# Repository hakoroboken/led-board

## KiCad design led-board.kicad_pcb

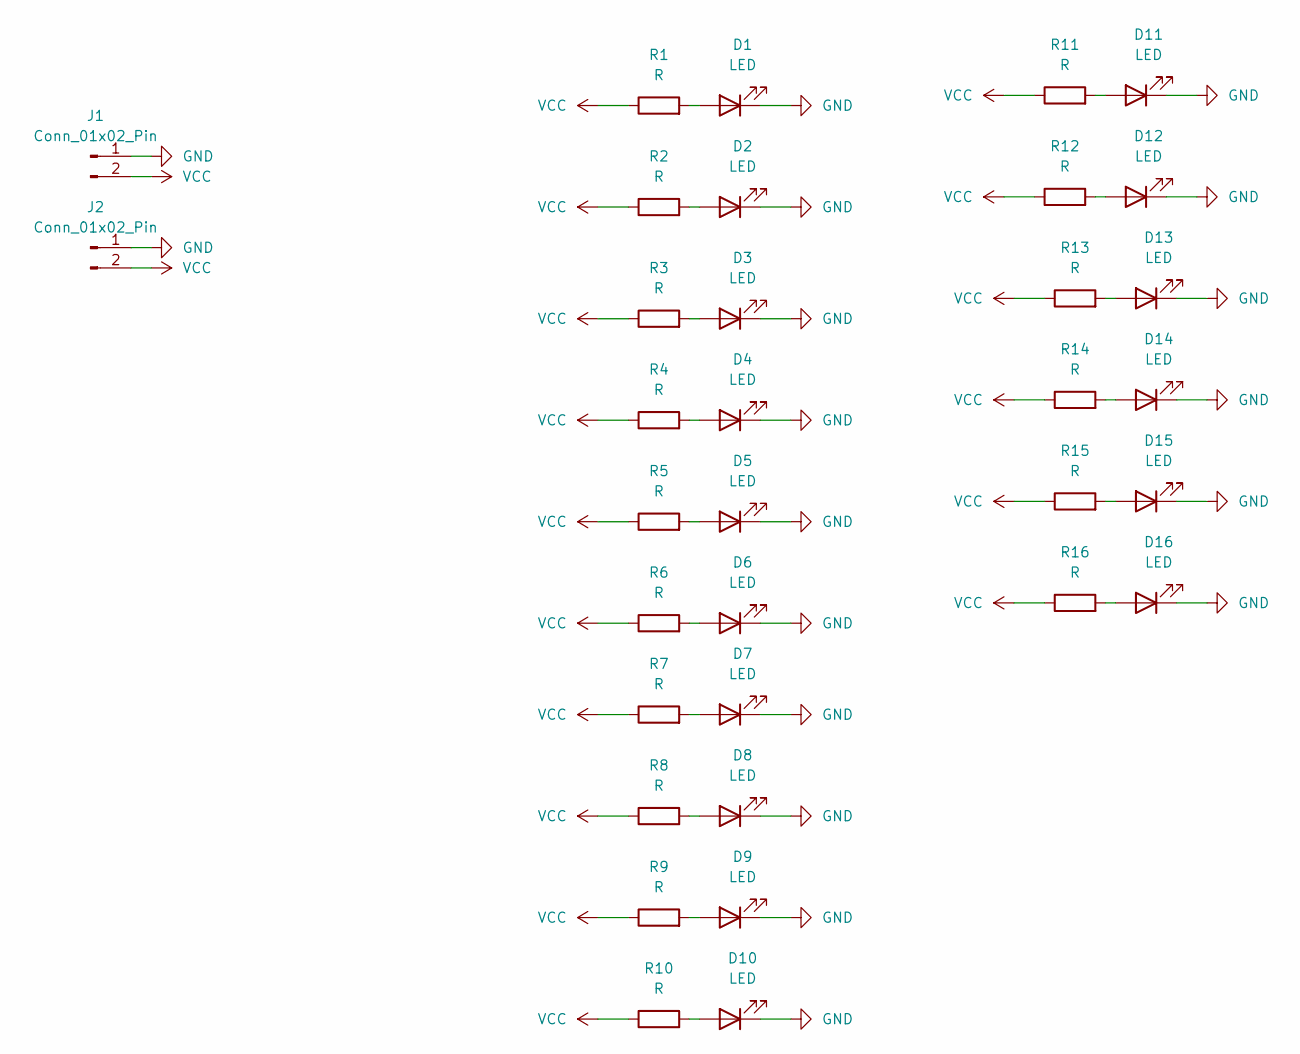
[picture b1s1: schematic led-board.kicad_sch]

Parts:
D1, D2, D3, D4, D5, D6, D7, D8, D9, D10, D11, D12, D13, D14, D15, D16: LED; LED_D5.0mm
J1, J2: Conn_01x02_Pin; AMASS_XT60PW-F_1x02_P7.20mm_Horizontal
R1, R2, R3, R4, R5, R6, R7, R8, R9, R10, R11, R12, R13, R14, R15, R16: R; R_Axial_DIN0207_L6.3mm_D2.5mm_P10.16mm_Horizontal

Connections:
GND: D1.1 (K), D2.1 (K), D3.1 (K), D4.1 (K), D5.1 (K), D6.1 (K), D7.1 (K), D8.1 (K), D9.1 (K), D10.1 (K), D11.1 (K), D12.1 (K), D13.1 (K), D14.1 (K), D15.1 (K), D16.1 (K), J1.1, J2.1
unnamed: D1.2 (A), R1.2
unnamed: D2.2 (A), R2.2
unnamed: D3.2 (A), R3.2
unnamed: D4.2 (A), R4.2
unnamed: D5.2 (A), R5.2
unnamed: D6.2 (A), R6.2
unnamed: D7.2 (A), R7.2
unnamed: D8.2 (A), R8.2
unnamed: D9.2 (A), R9.2
unnamed: D10.2 (A), R10.2
unnamed: D11.2 (A), R11.2
unnamed: D12.2 (A), R12.2
unnamed: D13.2 (A), R13.2
unnamed: D14.2 (A), R14.2
unnamed: D15.2 (A), R15.2
unnamed: D16.2 (A), R16.2
VCC: J1.2, J2.2, R1.1, R2.1, R3.1, R4.1, R5.1, R6.1, R7.1, R8.1, R9.1, R10.1, R11.1, R12.1, R13.1, R14.1, R15.1, R16.1

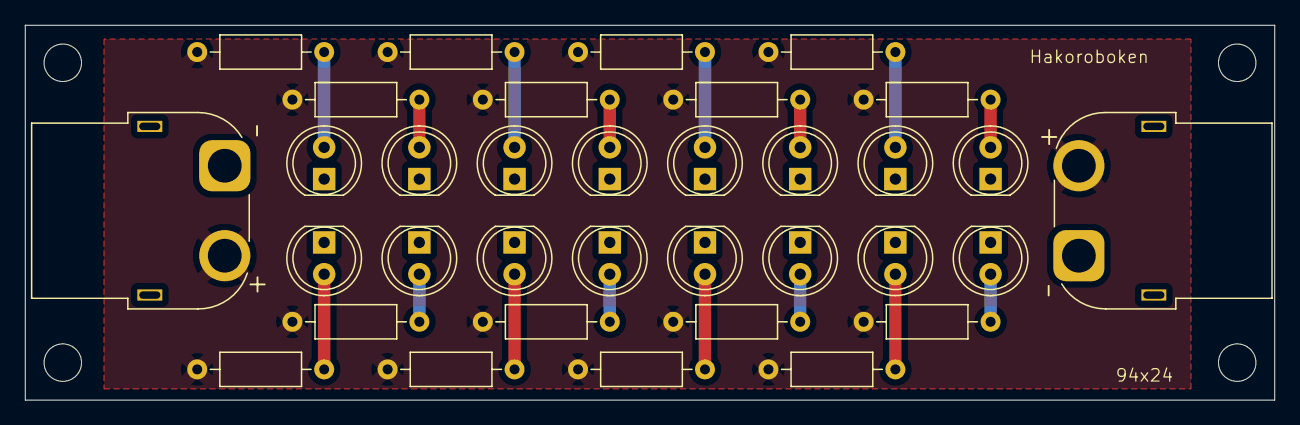
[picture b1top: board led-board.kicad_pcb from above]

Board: 2 copper layers, 100.0 x 30.0 mm, 34 parts (0 on the bottom side), 18 nets.
